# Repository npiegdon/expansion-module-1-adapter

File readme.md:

## ColecoVision Expansion Module #1 Stand-Alone Adapter 

**THIS PROJECT IS UNFINISHED AND DOESN'T WORK IN ITS CURRENT STATE!**

Inspired by [this AtariAge post](https://atariage.com/forums/topic/312955-expansion-module-1-standalone-project/) and because the Expansion Module #1 already has the whole card-edge connector exposed in the back, it seemed like it would be an improvement to make a simple card that could slot right into the back instead of drilling any holes (or even cracking the thing open).

Then, instead of a mod, it would be a simple little adapter box.

I laid the same circuit from the original post out on a new board, with the following changes:

1. The power input has been migrated to the "[best quality PS ever made for the ColecoVision](https://atariage.com/forums/topic/308050-285-watt-colecovision-compatible-power-supply-the-best-quality-ps-every-made-for-the-colecovision/)"  Mean Well GP25B13A-R1B power supply, which uses a DIN-5 connector.  The input voltages are already exactly correct, so the 5V regulator was dropped.  If you already own that replacement PSU for your ColecoVision, it can be used directly, as-is for your expansion module, too. 
2. Added the same power filtering present in the Colecovision.  (It's probably overkill, but better safe than sorry.)
3. The reset switch now employs simple debouncing.  The design in the AA post didn't have any and the ColecoVision itself uses a rather elaborate pulse-generator scheme, so I met in the middle and did the best I could with just a few passives.
4. All the parts are now sourced from Digi-Key (instead of several vendors), so they can be purchased in a single order.

## Unfinished Work

After building a prototype, it seemed to turn over just fine with the right voltages everywhere you might expect.  But while my Expansion Module #1 looks just fine when running through my ColecoVision, the output video was *very* dark when going through this adapter board.  Looking at the schematics for both, the video output from the expansion runs to exactly the point in the ColecoVision (RF header pin 6) where people are normally directed to tap the video signal when performing a composite video output mod.  So my guess is that this adapter board + the usual ColecoVision composite mod would do the trick.

I got most of the way through a breadboard implementation (with a THS7314 I had nearby), saw a too-bright picture, started to fiddle with trim pots, and eventually ran out of steam.  I was hoping for a simple board-layout project and not a protracted design project like [last time](https://tms-rgb.com), so I decided to cut my losses and post this here in its unfinished state.

So the only things missing before this could be considered complete:

1. Add the usual video amp with 75-ohm output just before the video output.
2. It might be nice to add the footprint for a TRRS jack (like [this one](https://www.digikey.com/product-detail/en/cui-devices/SJ-43514/CP-43514-ND/368146)) someplace on the board to give people an alternative to the RCA jacks.  It shaves about $3 off the $13 parts list and the same PCB could be used for both versions.
3. Design a 3D printable enclosure.

## Building One Anyway

It's all through-hole, every passive has the same value so you can't get anything mixed up, and the only part that could even be inserted the wrong way is the crystal oscillator.

### Parts

| part              | qty |   unit | model          | Digi-Key part | subtotal |
|:------------------|----:|-------:|:---------------|:--------------|---------:|
| Power switch      | 1   | $1.81  | GF-161-0005    | [CWI359-ND](https://www.digikey.com/product-detail/en/cw-industries/GF-161-0005/CWI359-ND/4089836)     | $1.81    |
| Reset switch      | 1   | $0.12  | 2-1825910-7    | [450-1642-ND](https://www.digikey.com/en/products/detail/te-connectivity-alcoswitch-switches/2-1825910-7/1632528)   | $0.12    |
| Oscillator        | 1   | $3.12  | ECS-2100A-035  | [XC235-ND](https://www.digikey.com/product-detail/en/ecs-inc/ECS-2100A-035/XC235-ND/31990)      | $3.12    |
| DIN5 port         | 1   | $2.63  | SDS-50J        | [CP-2350-ND](https://www.digikey.com/product-detail/en/cui-devices/SDS-50J/CP-2350-ND/97033)    | $2.63    |
| Composite L       | 1   | $1.36  | RCJ-042        | [CP-1419-ND](https://www.digikey.com/product-detail/en/cui-devices/RCJ-042/CP-1419-ND/408506)    | $1.36    |
| Composite R       | 1   | $1.36  | RCJ-043        | [CP-1420-ND](https://www.digikey.com/product-detail/en/cui-devices/RCJ-043/CP-1420-ND/408507)    | $1.36    |
| Composite Vid     | 1   | $1.36  | RCJ-044        | [CP-1421-ND](https://www.digikey.com/product-detail/en/cui-devices/RCJ-044/CP-1421-ND/408508)    | $1.36    |
| Inductor (10uH)   | 3   | $0.29  | 11R103C        | [811-2024-ND](https://www.digikey.com/product-detail/en/murata-power-solutions-inc/11R103C/811-2024-ND/1998211)   | $0.87    |
| Resistor (1k)     | 2   | $0.03  | jellybean      |               | $0.06    |
| Capacitor (0.1uF) | 8   | $0.03  | anything X7R   |               | $0.24    |
|                   |     |        |                | Total:        | **$12.93** |

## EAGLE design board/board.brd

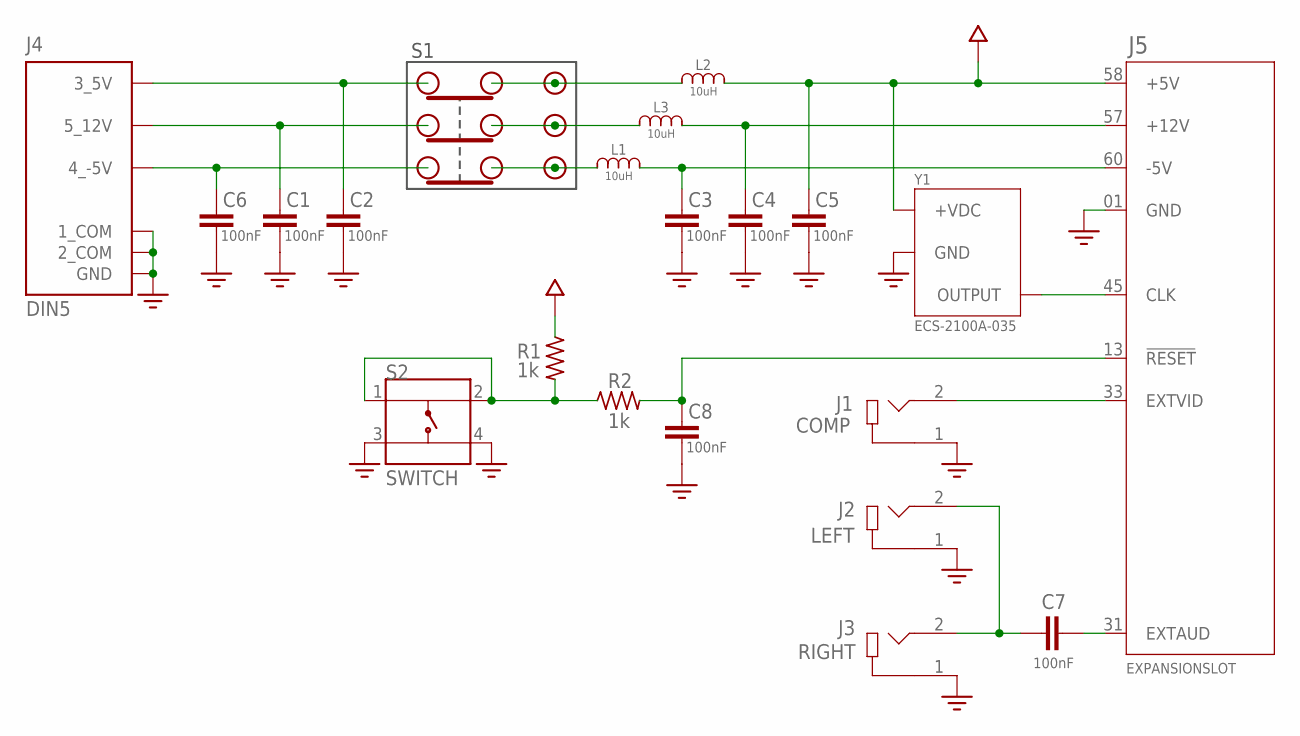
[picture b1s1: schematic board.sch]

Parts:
C1, C2, C3, C4, C5, C6, C7, C8: 100nF; C050-035X075
J1: COMP; CUI_RCJ-042
J2: LEFT; CUI_RCJ-042
J3: RIGHT; CUI_RCJ-042
J4: DIN5; CUI_SDS-50J
J5: EXPANSIONSLOT
L1, L2, L3: 10uH; 1100R_MUR
R1, R2: 1k; 0207/10
S1: 3PDT
S2: SWITCH; SW_2-1825910-7
Y1: ECS-2100A-035; OSC_ECS-2100A-035

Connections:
5V: C5.1, J5.58 (+5V), L2.1, R1.1, Y1.8 (+VDC)
5V_IN: C2.1, J4.3 (3_5V), S1.P$1C
12V: C4.1, J5.57 (+12V), L3.1
12V_IN2: C1.1, J4.5 (5_12V), S1.P$2C
GND: C1.2, C2.2, C3.2, C4.2, C5.2, C6.2, C8.2, J1.1, J2.1, J3.1, J4.1 (1_COM), J4.2 (2_COM), J4.E1 (GND), J4.E2 (GND), J5.01 (GND), S2.3, S2.4, Y1.4 (GND)
M5V2: C3.1, J5.60 (-5V), L1.1
M5V_IN: C6.1, J4.4 (4_-5V), S1.P$3C
unnamed: L1.2, S1.P$3A, S1.P$3B
unnamed: L3.2, S1.P$2A, S1.P$2B
unnamed: L2.2, S1.P$1A, S1.P$1B
unnamed: R1.2, R2.1, S2.1, S2.2
unnamed: J5.45 (CLK), Y1.5 (OUTPUT)
unnamed: J1.2, J5.33 (EXTVID)
unnamed: C7.1, J5.31 (EXTAUD)
unnamed: C8.1, J5.13 (!RESET), R2.2
unnamed: C7.2, J2.2, J3.2

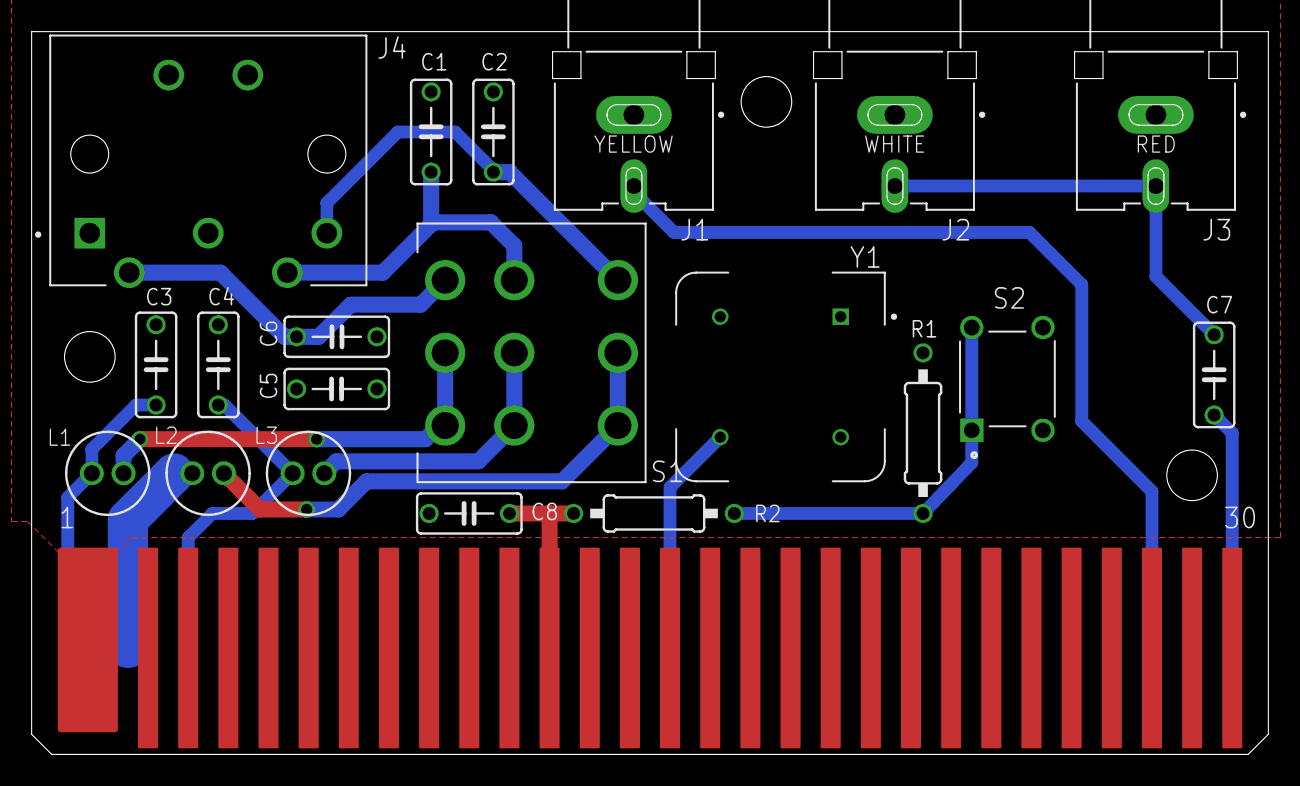
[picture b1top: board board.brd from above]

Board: 2 copper layers, 78.2 x 45.7 mm, 21 parts (0 on the bottom side), 16 nets.

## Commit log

2021-02-06 Initial add
